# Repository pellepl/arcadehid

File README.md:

arcadehid
=========

STM32 HID device for arcade builds

Compound HID device containing keyboard, mouse, two joysticks and a virtual com port. Plug into a retropie or something and wire cool buttons and joysticks and whatnot.

See /cad - here you'll find a reference design with 26 pins for an STM32F1 128kB flash variant. Any STM32F1 board would do, as long as pin-headers are broken out.

Each pin can be configured with combinations of a keyboard keypress, mouse movement or click, or joystick movement or button press.

Every pin can hold up to eight different combinations. There is also ternary support meaning a pin's config can change depending on if another pin is active or not.

Accelerators for mouse and joystick are supported.

Everything is configured in the command line interface, either via UART pins or via virtual com port.

Different configurations can be saved and loaded, using the internal flash of the STM32F1 (128 kb variant) - no extra storage chip needed.

Depends on pellepl/generic_embedded and pellepl/niffs.

Now also with the Annoyatron support, drive your friends mad...

CLI pin definition examples
===========================
```
// define pin 1 to send keyboard character A
def pin1 = a
// define pin 2 to move mouse up
def pin2 = mouse_y(-1)
// define pin 3 to move mouse right if pin 4 is pressed else left
def pin3 = pin4 ? mouse_x(1) : mouse_x(-1)
// define pin 5 to send keyboard sequence CTRL+ALT+DEL
def pin5 = LEFT_CTRL LEFT_ALT DELETE
```

For certain definitions, numerators are possible. A numerators normally tells how much to move something, e.g. a mouse or joystick. In addition, all numerators can have accelerators, meaning the control will move more and more over time.
A numerator ```<num>``` is defined as  ```(ACC)[(+)|-][1..127]```.

```
// move joystick 10 steps right on x axis
def pin7 = joy1_x(10)
// move joystick accelerating from 1 to 10 steps right on x axis
def pin8 = joy1_x(ACC10)
// and left
def pin8 = joy1_x(ACC-10)
```

Accelerator speed is controlled by cli commands
```
set_mouse_pos_acc
set_mouse_wheel_acc
set_joy_acc
```

Following is a list of all definitions possible.

```
KEYBOARD SYMBOLS:
  A                   B                   C                   D                   
  E                   F                   G                   H                   
  I                   J                   K                   L                   
  M                   N                   O                   P                   
  Q                   R                   S                   T                   
  U                   V                   W                   X                   
  Y                   Z                   1                   2                   
  3                   4                   5                   6                   
  7                   8                   9                   0                   
  ENTER               ESCAPE              BACKSPACE           TAB                 
  SPACE               MINUS               EQUAL               LEFTBRACKET         
  RIGHTBRACKET        BACKSLASH           NONUS_HASH          SEMICOLON           
  QUOTE               GRAVE               COMMA               DOT                 
  SLASH               CAPSLOCK            F1                  F2                  
  F3                  F4                  F5                  F6                  
  F7                  F8                  F9                  F10                 
  F11                 F12                 PRINTSCREEN         SCROLLLOCK          
  PAUSE               INSERT              HOME                PGUP                
  DELETE              END                 PGDOWN              RIGHT               
  LEFT                DOWN                UP                  NUMLOCK             
  KP_SLASH            KP_ASTERISK         KP_MINUS            KP_PLUS             
  KP_ENTER            KP_1                KP_2                KP_3                
  KP_4                KP_5                KP_6                KP_7                
  KP_8                KP_9                KP_0                KP_DOT              
  NONUS_BACKSLASH     APPLICATION         POWER               KP_EQUAL            
  F13                 F14                 F15                 F16                 
  F17                 F18                 F19                 F20                 
  F21                 F22                 F23                 F24                 
  EXECUTE             HELP                MENU                SELECT              
  STOP                AGAIN               UNDO                CUT                 
  COPY                PASTE               FIND                MUTE                
  VOLUME_UP           VOLUME_DOWN         LOCKING_CAPS        LOCKING_NUM         
  LOCKING_SCROLL      KP_COMMA            KP_EQUAL_AS400      INT1                
  INT2                INT3                INT4                INT5                
  INT6                INT7                INT8                INT9                
  LANG1               LANG2               LANG3               LANG4               
  LANG5               LANG6               LANG7               LANG8               
  LANG9               ALT_ERASE           SYSREQ              CANCEL              
  CLEAR               PRIOR               RETURN              SEPARATOR           
  OUT                 OPER                CLEAR_AGAIN         CRSEL               
  EXSEL               SYSTEM_POWER        SYSTEM_SLEEP        SYSTEM_WAKE         
  AUDIO_MUTE          AUDIO_VOL_UP        AUDIO_VOL_DOWN      MEDIA_NEXT_TRACK    
  MEDIA_PREV_TRACK    MEDIA_STOP          MEDIA_PLAY_PAUSE    MEDIA_SELECT        
  MEDIA_EJECT         MAIL                CALCULATOR          MY_COMPUTER         
  WWW_SEARCH          WWW_HOME            WWW_BACK            WWW_FORWARD         
  WWW_STOP            WWW_REFRESH         WWW_FAVORITES       MEDIA_FAST_FORWARD  
  MEDIA_REWIND        LEFT_CTRL           LEFT_SHIFT          LEFT_ALT            
  LEFT_GUI            RIGHT_CTRL          RIGHT_SHIFT         RIGHT_ALT           
  RIGHT_GUI           

MOUSE SYMBOLS:
  MOUSE_X(<num>)      MOUSE_Y(<num>)      MOUSE_BUTTON1       MOUSE_BUTTON2       
  MOUSE_BUTTON3       MOUSE_WHEEL(<num>)  

JOYSTICK SYMBOLS:
  JOY1_X(<num>)       JOY1_Y(<num>)       JOY1_BUTTON1        JOY1_BUTTON2        
  JOY1_BUTTON3        JOY1_BUTTON4        JOY1_BUTTON5        JOY1_BUTTON6        
  JOY1_BUTTON7        JOY1_BUTTON8        JOY1_BUTTON9        JOY1_BUTTON10       
  JOY1_BUTTON11       JOY1_BUTTON12       JOY1_BUTTON13       JOY1_BUTTON14       
  JOY2_X(<num>)       JOY2_Y(<num>)       JOY2_BUTTON1        JOY2_BUTTON2        
  JOY2_BUTTON3        JOY2_BUTTON4        JOY2_BUTTON5        JOY2_BUTTON6        
  JOY2_BUTTON7        JOY2_BUTTON8        JOY2_BUTTON9        JOY2_BUTTON10       
  JOY2_BUTTON11       JOY2_BUTTON12       JOY2_BUTTON13       JOY2_BUTTON14
```

## Building ##

Make sure you clone submodules.

```
human-entity@machine ~$ git clone --recursive https://github.com/pellepl/arcadehid
```

You'll need an arm toolchain, let's say it lies in `/home/human-entity/toolchain/arm-none-eabi-toolchain-gcc-6.3.0`.
Then you simply do this:
```
human-entity@machine ~$ cd arcadehid
human-entity@machine ~/arcadehid$ make clean
human-entity@machine ~/arcadehid$ CROSS_COMPILE=/home/human-entity/toolchain/arm-none-eabi-toolchain-gcc-6.3.0/bin/arm-none-eabi- make all
```

Alternatively. you tinker a bit with the makefile.

This will produce target files in elf, binary, and ihex flavours in the `build` folder. Flash using your favourite dongle and tool. I use OpenOCD, there are some scripts in the repo which might be helpful to others.

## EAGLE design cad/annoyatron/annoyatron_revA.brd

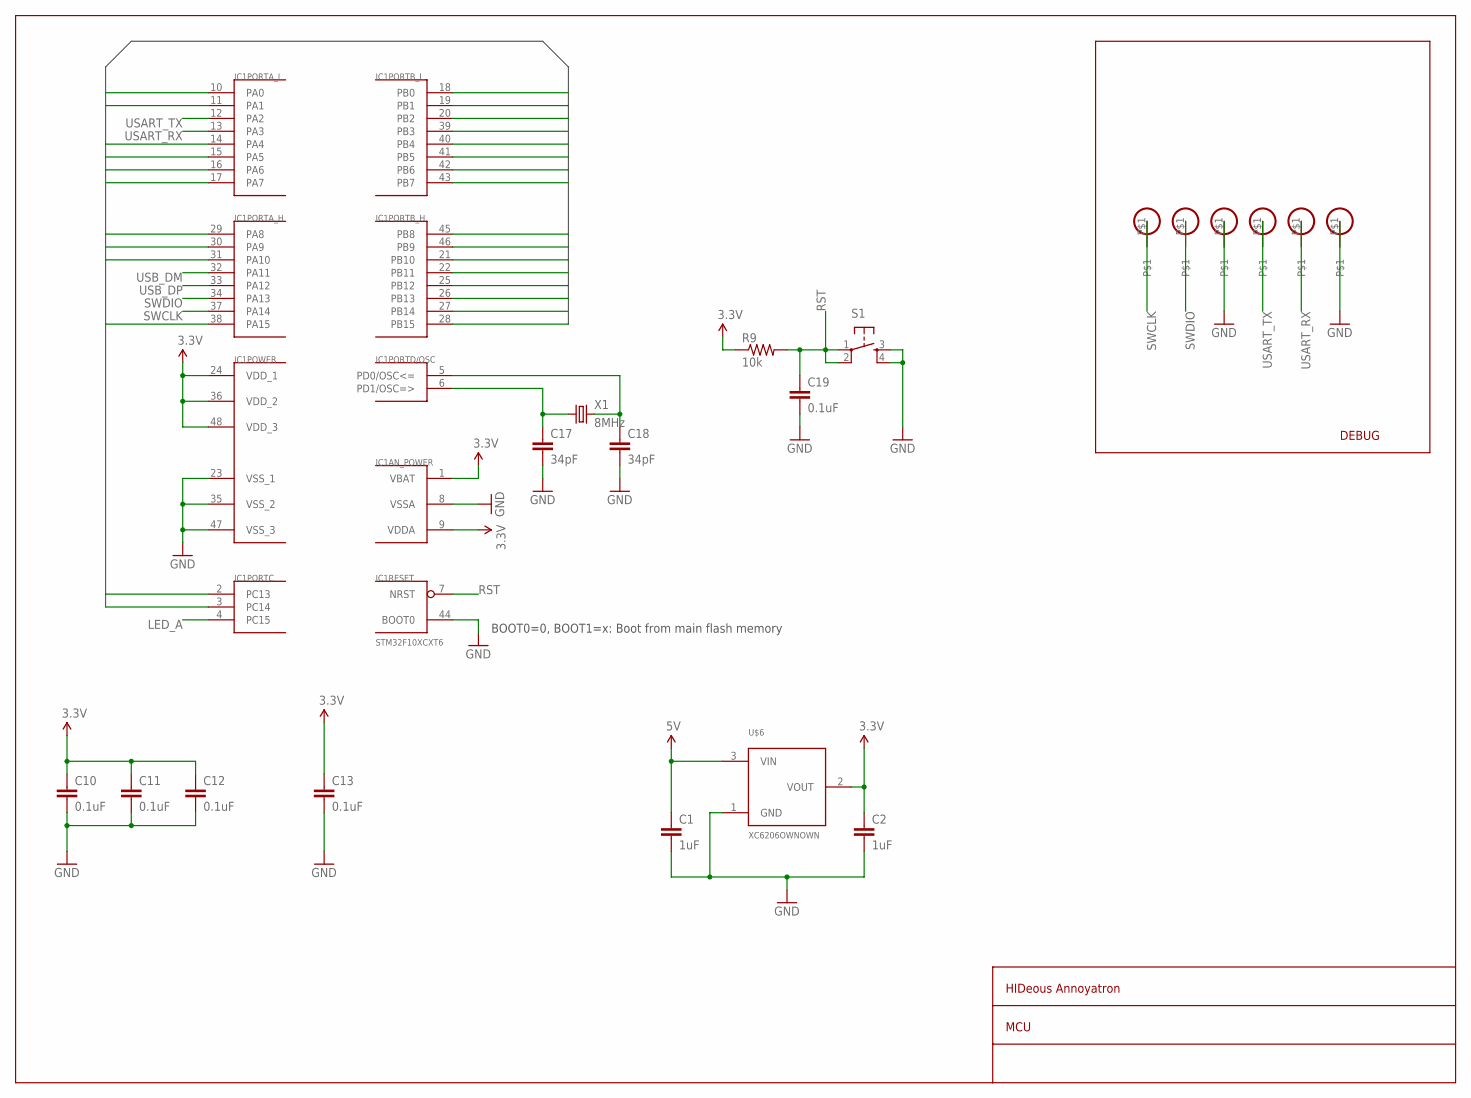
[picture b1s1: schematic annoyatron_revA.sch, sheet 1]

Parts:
C1, C2: 1uF; 0805_GEN
C10, C11, C12, C13, C19: 0.1uF; C0402
C17, C18: 34pF; C0402
IC1: STM32F10XCXT6; TQFP48
R9: 10k; C0402
S1: TAC_SWITCHSMD; TACTILE_SWITCH_SMD
U$2, U$3, U$4, U$5, U$9, U$10: PADOWN; PAD2MM
U$6: XC6206OWNOWN; SOT23
X1: 8MHz; CRYSTAL_SMD_5X3.2_7A

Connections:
3.3V: C2.1, C10.1, C11.1, C12.1, C13.1, IC1.1 (VBAT), IC1.9 (VDDA), IC1.24 (VDD_1), IC1.36 (VDD_2), IC1.48 (VDD_3), R9.1, U$6.2 (VOUT)
5V: C1.1, U$6.3 (VIN); also elsewhere on the board
GND: C1.2, C2.2, C10.2, C11.2, C12.2, C13.2, C17.2, C18.2, C19.2, IC1.8 (VSSA), IC1.23 (VSS_1), IC1.35 (VSS_2), IC1.44 (BOOT0), IC1.47 (VSS_3), S1.3, S1.4, U$4.P$1, U$6.1 (GND), U$10.P$1; also elsewhere on the board
LED_A: IC1.4 (PC15)
OSCI: C18.1, IC1.5 (PD0/OSC<=), X1.P$2 (2)
OSCO: C17.1, IC1.6 (PD1/OSC=>), X1.P$1 (1)
PA0: IC1.10 (PA0)
PA1: IC1.11 (PA1)
PA4: IC1.14 (PA4)
PA5: IC1.15 (PA5)
PA6: IC1.16 (PA6)
PA7: IC1.17 (PA7)
PA8: IC1.29 (PA8); also elsewhere on the board
PA9: IC1.30 (PA9)
PA10: IC1.31 (PA10)
PA15: IC1.38 (PA15)
PB0: IC1.18 (PB0)
PB1: IC1.19 (PB1)
PB2: IC1.20 (PB2)
PB3: IC1.39 (PB3)
PB4: IC1.40 (PB4)
PB5: IC1.41 (PB5)
PB6: IC1.42 (PB6)
PB7: IC1.43 (PB7)
PB8: IC1.45 (PB8)
PB9: IC1.46 (PB9)
PB10: IC1.21 (PB10)
PB11: IC1.22 (PB11)
PB12: IC1.25 (PB12)
PB13: IC1.26 (PB13)
PB14: IC1.27 (PB14)
PB15: IC1.28 (PB15)
PC13: IC1.2 (PC13)
PC14: IC1.3 (PC14)
RST: C19.1, IC1.7 (NRST), R9.2, S1.1, S1.2
SWCLK: IC1.37 (PA14), U$2.P$1
SWDIO: IC1.34 (PA13), U$3.P$1
USART_RX: IC1.13 (PA3), U$9.P$1
USART_TX: IC1.12 (PA2), U$5.P$1
USB_DM: IC1.32 (PA11); also elsewhere on the board
USB_DP: IC1.33 (PA12); also elsewhere on the board

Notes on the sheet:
HIDeous Annoyatron
MCU
DEBUG
BOOT0=0, BOOT1=x: Boot from main flash memory

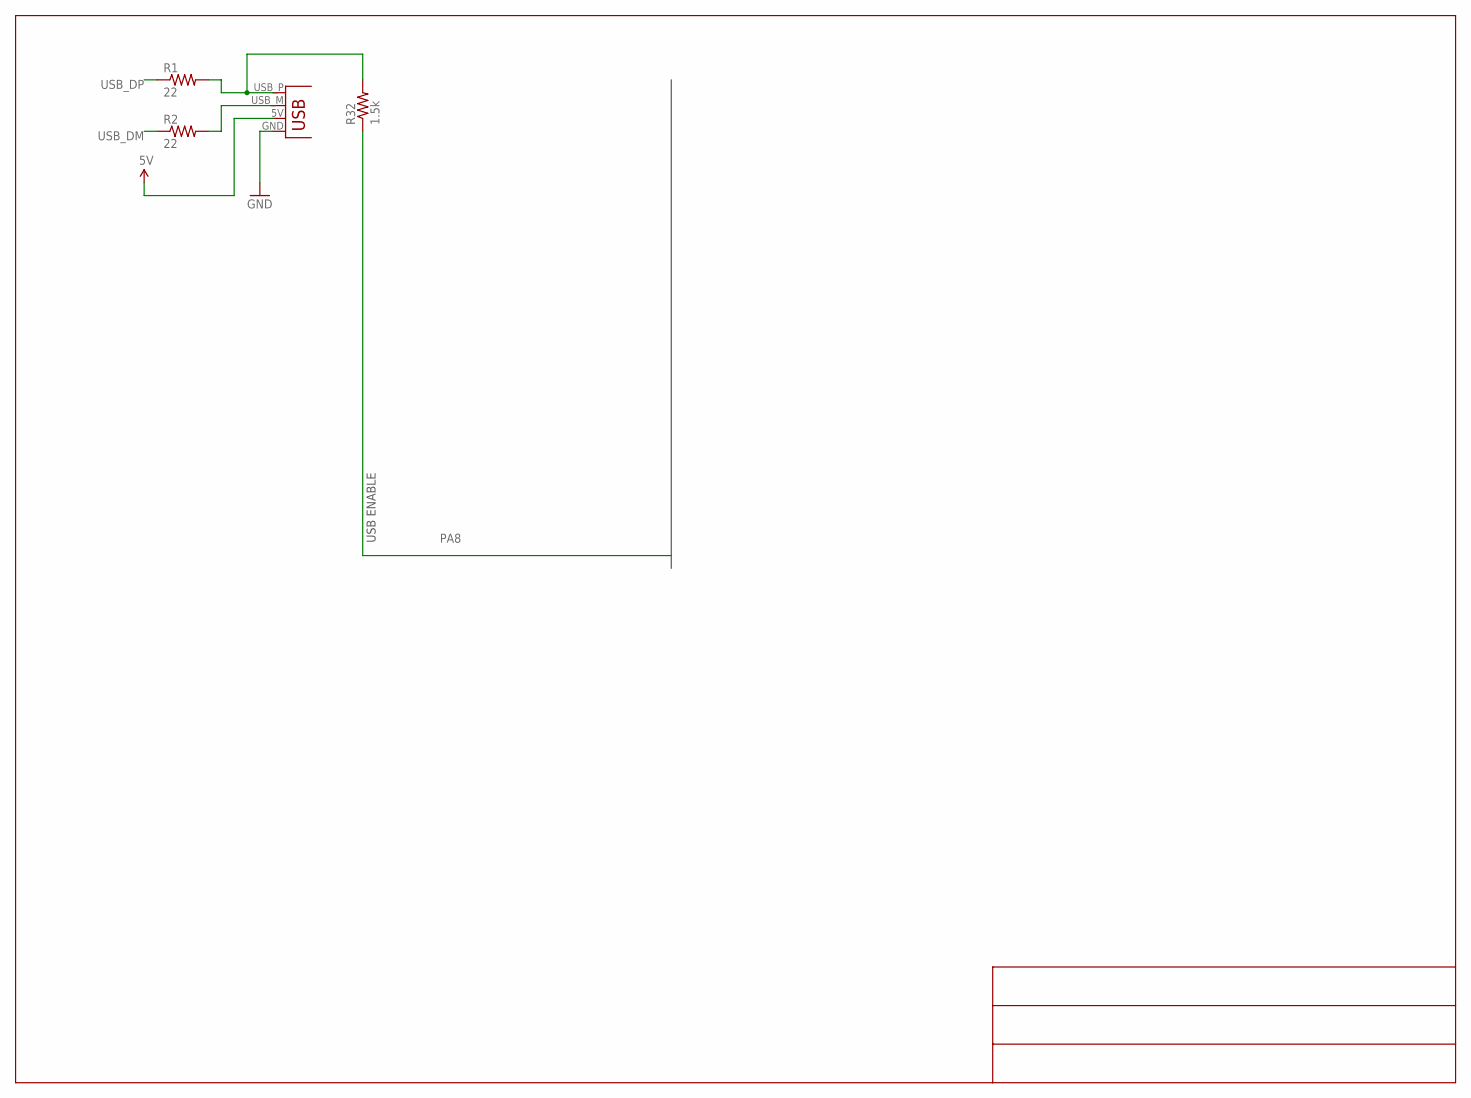
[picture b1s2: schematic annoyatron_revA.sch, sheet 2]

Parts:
JP1: USBPCB; USB-A-PCB
R1, R2: 22; C0402
R32: 1.5k; C0402

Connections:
5V: JP1.5V (VBUS); also elsewhere on the board
GND: JP1.GND; also elsewhere on the board
unnamed: JP1.USB_P (D+), R1.2, R32.2
unnamed: JP1.USB_M (D-), R2.2
PA8: R32.1; also elsewhere on the board
USB_DM: R2.1; also elsewhere on the board
USB_DP: R1.1; also elsewhere on the board

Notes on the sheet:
USB ENABLE

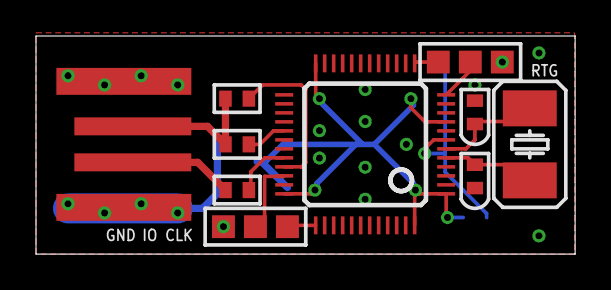
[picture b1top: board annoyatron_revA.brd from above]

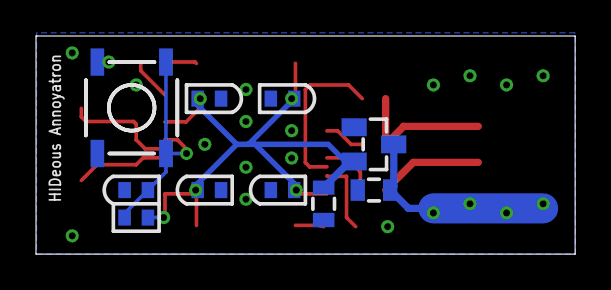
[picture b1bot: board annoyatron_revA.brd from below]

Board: 2 copper layers, 30.0 x 12.1 mm, 24 parts (10 on the bottom side), 15 nets.

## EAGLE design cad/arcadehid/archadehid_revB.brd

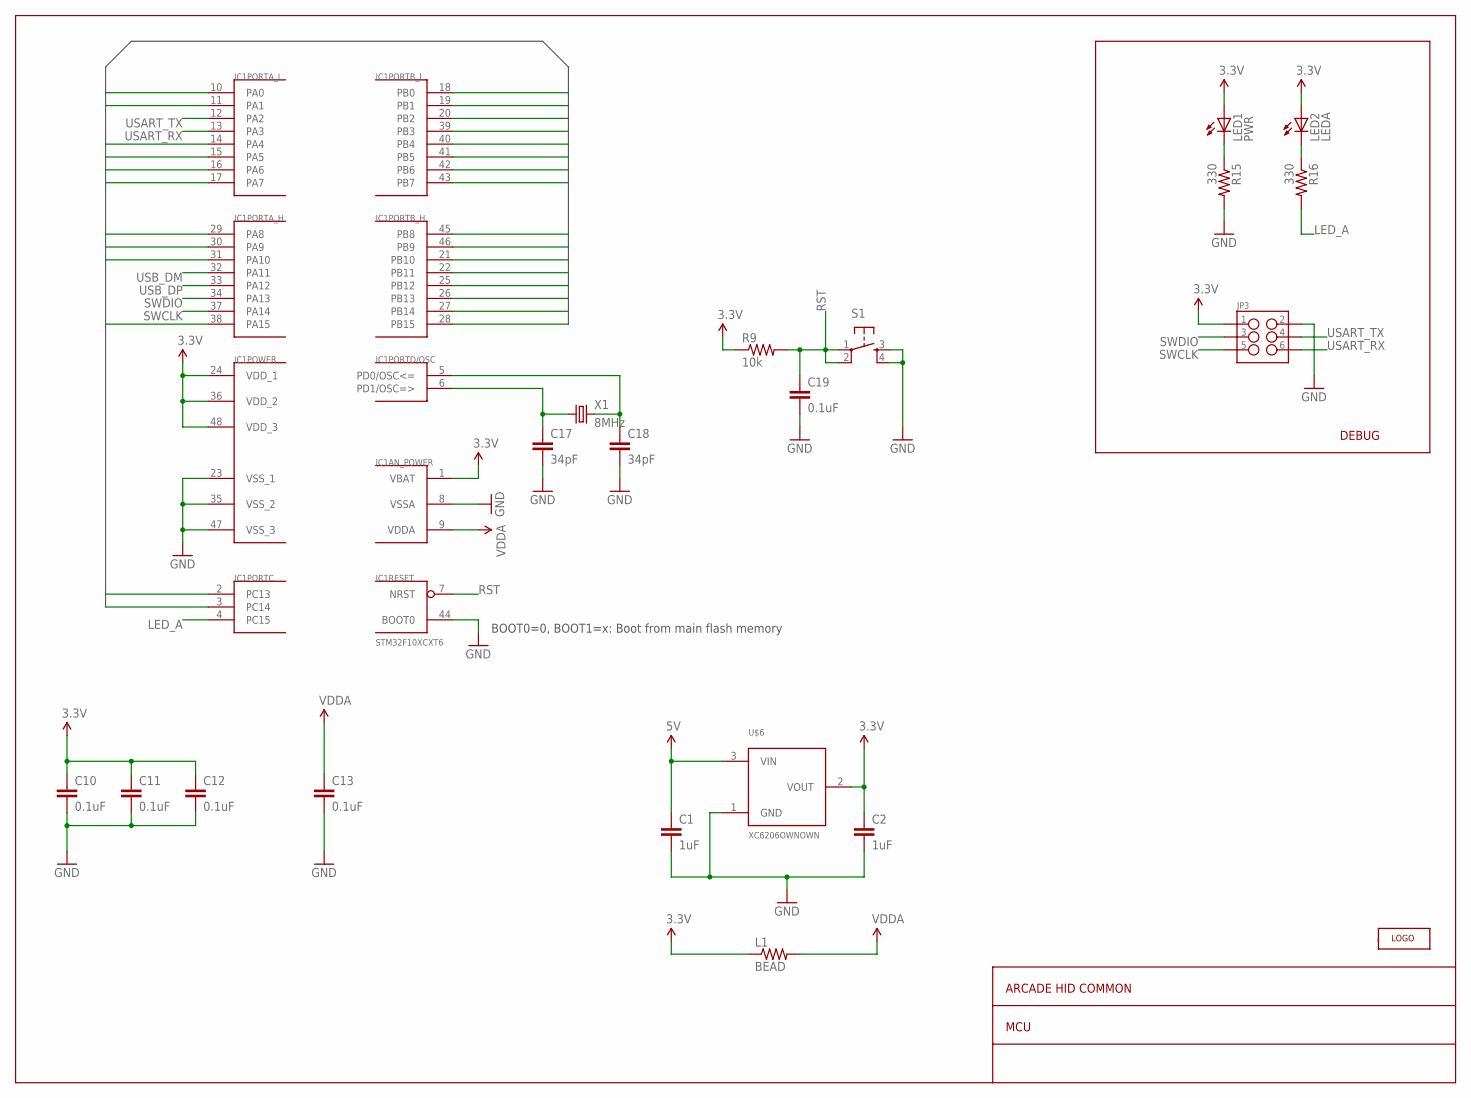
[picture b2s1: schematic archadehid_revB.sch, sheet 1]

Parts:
C1, C2: 1uF; 0805_GEN
C10, C11, C12, C13, C19: 0.1uF; C0402
C17, C18: 34pF; C0402
IC1: STM32F10XCXT6; TQFP48
JP3: M03X2NO_SILK; 2X3-NS
L1: BEAD; 0603_GEN
LED1: PWR; LED-0603
LED2: LEDA; LED-0603
R9: 10k; C0402
R15, R16: 330; C0402
S1: TAC_SWITCHSMD; TACTILE_SWITCH_SMD
U$6: XC6206OWNOWN; SOT23
U$7: LOGOLOGO; LOGO
X1: 8MHz; CRYSTAL_SMD_5X3.2_7A

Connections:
3.3V: C2.1, C10.1, C11.1, C12.1, IC1.1 (VBAT), IC1.24 (VDD_1), IC1.36 (VDD_2), IC1.48 (VDD_3), JP3.1, L1.1, LED1.A, LED2.A, R9.1, U$6.2 (VOUT); also elsewhere on the board
5V: C1.1, U$6.3 (VIN); also elsewhere on the board
GND: C1.2, C2.2, C10.2, C11.2, C12.2, C13.2, C17.2, C18.2, C19.2, IC1.8 (VSSA), IC1.23 (VSS_1), IC1.35 (VSS_2), IC1.44 (BOOT0), IC1.47 (VSS_3), JP3.2, R15.2, S1.3, S1.4, U$6.1 (GND); also elsewhere on the board
LED_A: IC1.4 (PC15), R16.2
unnamed: LED1.C, R15.1
unnamed: LED2.C, R16.1
OSCI: C18.1, IC1.5 (PD0/OSC<=), X1.P$2 (2)
OSCO: C17.1, IC1.6 (PD1/OSC=>), X1.P$1 (1)
PA0: IC1.10 (PA0); also elsewhere on the board
PA1: IC1.11 (PA1); also elsewhere on the board
PA4: IC1.14 (PA4); also elsewhere on the board
PA5: IC1.15 (PA5); also elsewhere on the board
PA6: IC1.16 (PA6); also elsewhere on the board
PA7: IC1.17 (PA7); also elsewhere on the board
PA8: IC1.29 (PA8); also elsewhere on the board
PA9: IC1.30 (PA9); also elsewhere on the board
PA10: IC1.31 (PA10); also elsewhere on the board
PA15: IC1.38 (PA15); also elsewhere on the board
PB0: IC1.18 (PB0); also elsewhere on the board
PB1: IC1.19 (PB1); also elsewhere on the board
PB2: IC1.20 (PB2); also elsewhere on the board
PB3: IC1.39 (PB3); also elsewhere on the board
PB4: IC1.40 (PB4); also elsewhere on the board
PB5: IC1.41 (PB5); also elsewhere on the board
PB6: IC1.42 (PB6); also elsewhere on the board
PB7: IC1.43 (PB7); also elsewhere on the board
PB8: IC1.45 (PB8)
PB9: IC1.46 (PB9); also elsewhere on the board
PB10: IC1.21 (PB10); also elsewhere on the board
PB11: IC1.22 (PB11); also elsewhere on the board
PB12: IC1.25 (PB12); also elsewhere on the board
PB13: IC1.26 (PB13); also elsewhere on the board
PB14: IC1.27 (PB14); also elsewhere on the board
PB15: IC1.28 (PB15); also elsewhere on the board
PC13: IC1.2 (PC13); also elsewhere on the board
PC14: IC1.3 (PC14); also elsewhere on the board
RST: C19.1, IC1.7 (NRST), R9.2, S1.1, S1.2
SWCLK: IC1.37 (PA14), JP3.5
SWDIO: IC1.34 (PA13), JP3.3
USART_RX: IC1.13 (PA3), JP3.6
USART_TX: IC1.12 (PA2), JP3.4
USB_DM: IC1.32 (PA11); also elsewhere on the board
USB_DP: IC1.33 (PA12); also elsewhere on the board
VDDA: C13.1, IC1.9 (VDDA), L1.2

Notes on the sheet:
ARCADE HID COMMON
MCU
DEBUG
BOOT0=0, BOOT1=x: Boot from main flash memory

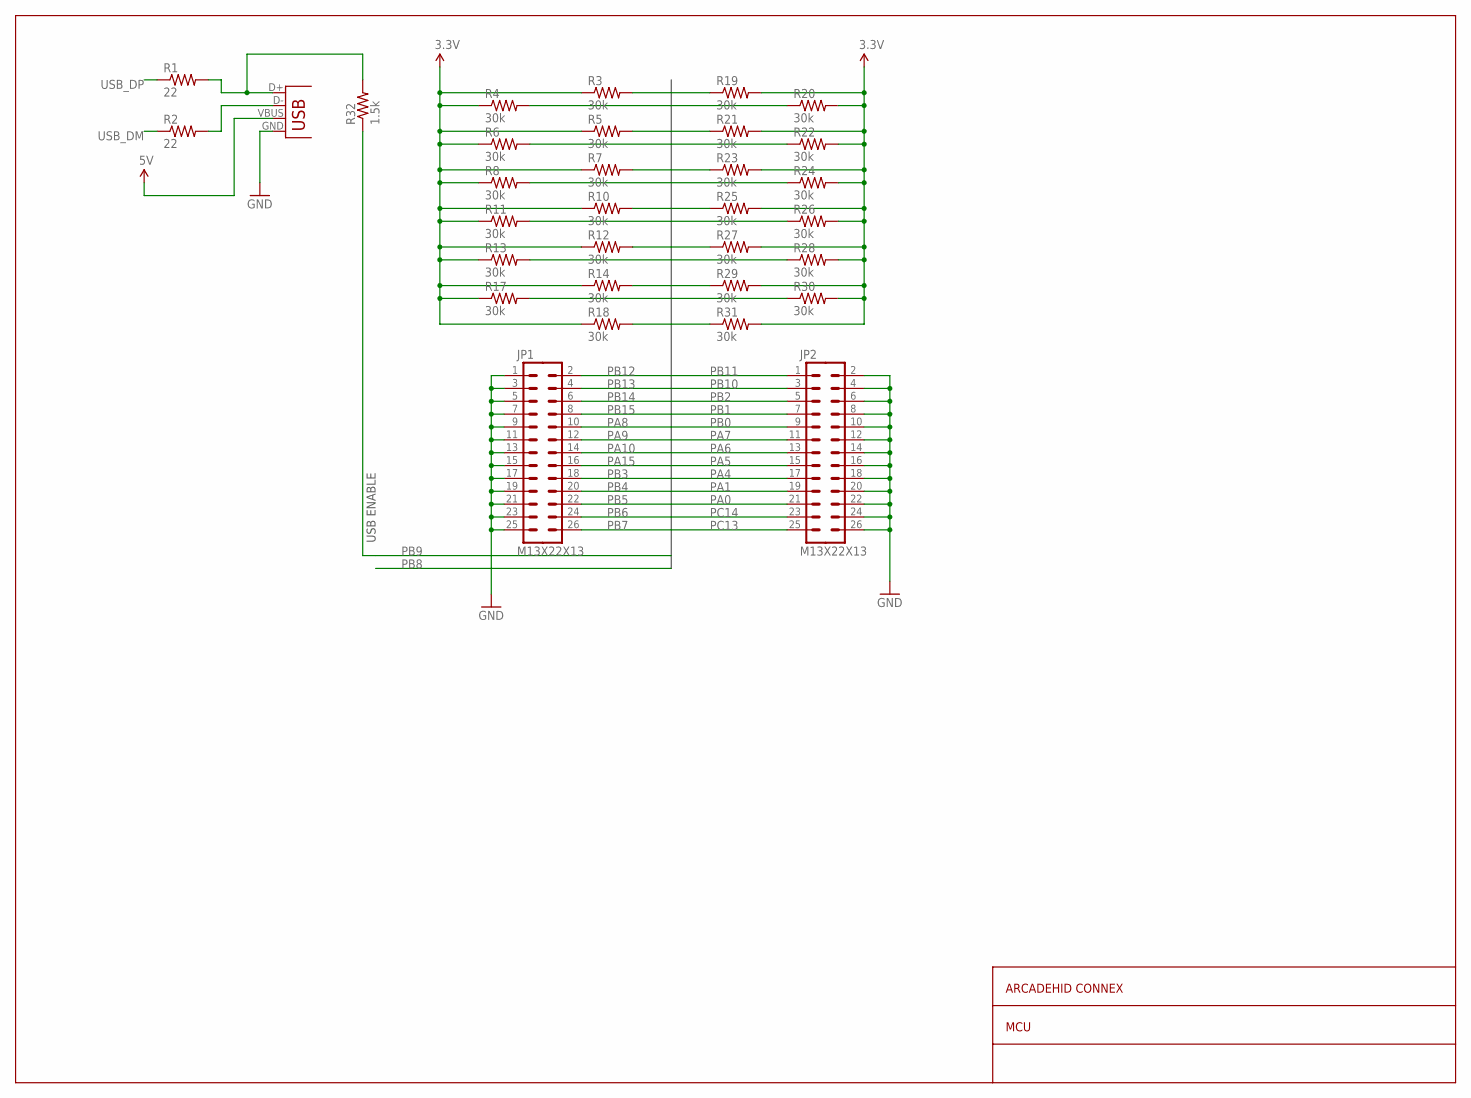
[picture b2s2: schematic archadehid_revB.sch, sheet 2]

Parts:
JP1, JP2: M13X22X13; 2X13
R1, R2: 22; C0402
R3, R4, R5, R6, R7, R8, R10, R11, R12, R13, R14, R17, R18, R19, R20, R21, R22, R23, R24, R25, R26, R27, R28, R29, R30, R31: 30k; C0402
R32: 1.5k; C0402
X3: USB-MINIB

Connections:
3.3V: R3.1, R4.1, R5.1, R6.1, R7.1, R8.1, R10.1, R11.1, R12.1, R13.1, R14.1, R17.1, R18.1, R19.2, R20.2, R21.2, R22.2, R23.2, R24.2, R25.2, R26.2, R27.2, R28.2, R29.2, R30.2, R31.2; also elsewhere on the board
5V: X3.VBUS; also elsewhere on the board
GND: JP1.1, JP1.3, JP1.5, JP1.7, JP1.9, JP1.11, JP1.13, JP1.15, JP1.17, JP1.19, JP1.21, JP1.23, JP1.25, JP2.2, JP2.4, JP2.6, JP2.8, JP2.10, JP2.12, JP2.14, JP2.16, JP2.18, JP2.20, JP2.22, JP2.24, JP2.26, X3.GND; also elsewhere on the board
unnamed: R1.2, R32.2, X3.D+
unnamed: R2.2, X3.D-
PA0: JP2.21, R29.1; also elsewhere on the board
PA1: JP2.19, R28.1; also elsewhere on the board
PA4: JP2.17, R27.1; also elsewhere on the board
PA5: JP2.15, R26.1; also elsewhere on the board
PA6: JP2.13, R25.1; also elsewhere on the board
PA7: JP2.11, R24.1; also elsewhere on the board
PA8: JP1.10, R7.2; also elsewhere on the board
PA9: JP1.12, R8.2; also elsewhere on the board
PA10: JP1.14, R10.2; also elsewhere on the board
PA15: JP1.16, R11.2; also elsewhere on the board
PB0: JP2.9, R23.1; also elsewhere on the board
PB1: JP2.7, R22.1; also elsewhere on the board
PB2: JP2.5, R21.1; also elsewhere on the board
PB3: JP1.18, R12.2; also elsewhere on the board
PB4: JP1.20, R13.2; also elsewhere on the board
PB5: JP1.22, R14.2; also elsewhere on the board
PB6: JP1.24, R17.2; also elsewhere on the board
PB7: JP1.26, R18.2; also elsewhere on the board
PB9: R32.1; also elsewhere on the board
PB10: JP2.3, R20.1; also elsewhere on the board
PB11: JP2.1, R19.1; also elsewhere on the board
PB12: JP1.2, R3.2; also elsewhere on the board
PB13: JP1.4, R4.2; also elsewhere on the board
PB14: JP1.6, R5.2; also elsewhere on the board
PB15: JP1.8, R6.2; also elsewhere on the board
PC13: JP2.25, R31.1; also elsewhere on the board
PC14: JP2.23, R30.1; also elsewhere on the board
USB_DM: R2.1; also elsewhere on the board
USB_DP: R1.1; also elsewhere on the board

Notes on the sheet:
ARCADEHID CONNEX
MCU
USB ENABLE

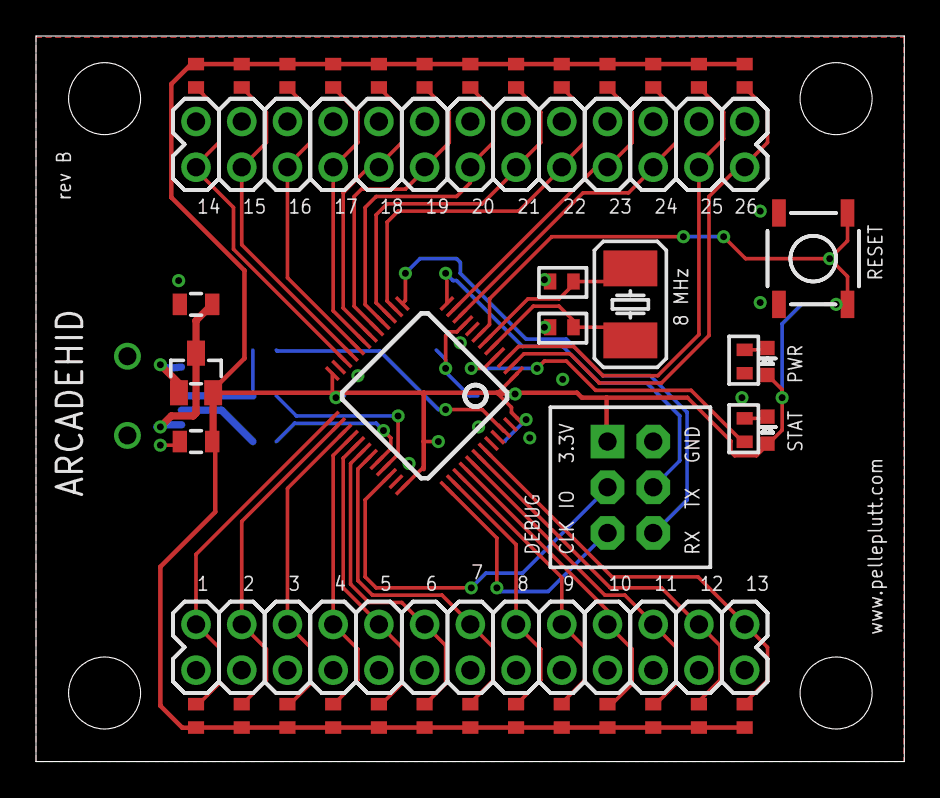
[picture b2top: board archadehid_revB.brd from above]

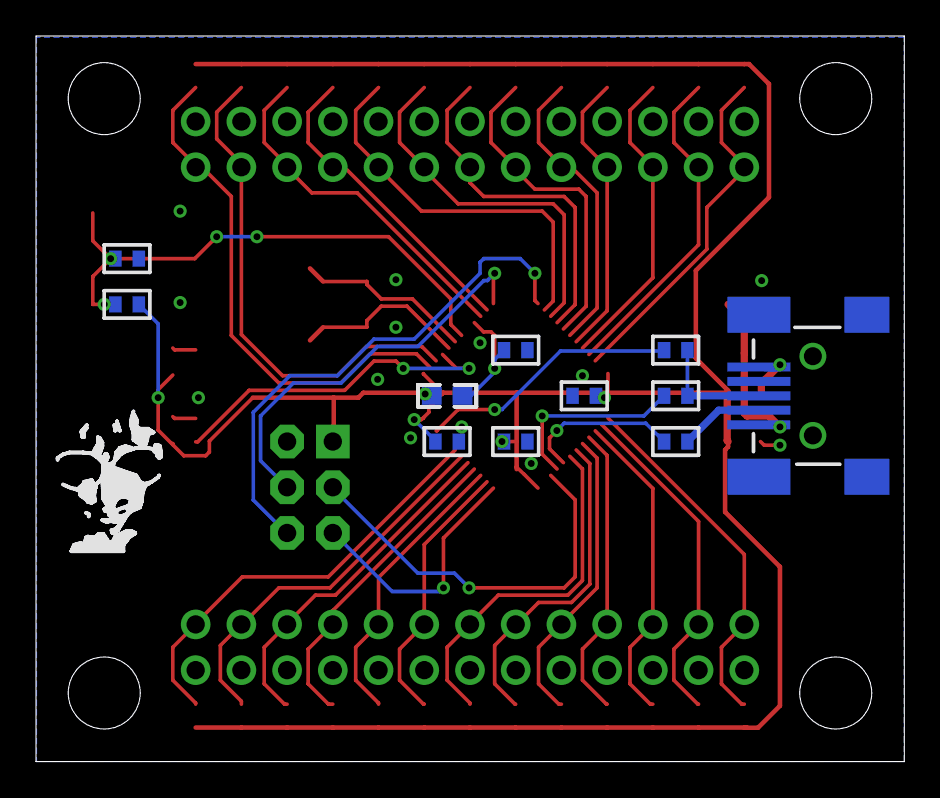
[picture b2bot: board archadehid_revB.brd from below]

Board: 2 copper layers, 48.2 x 40.3 mm, 53 parts (12 on the bottom side), 45 nets.

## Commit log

2014-12-29 inital commit
2014-12-29 cleanup, reset @ assert
2014-12-30 getting ledstate
2015-01-02 added mouse configuration
2015-01-07 cadding, almost there
2015-01-07 minor cleanups
2015-01-08 cad, rev A to factory
2015-01-09 embryo for adding usb vcd, build configurable
2015-01-09 usb cdc acm profile working
2015-01-09 added usb serial as io
2015-01-09 clean away windows lineendings
2015-01-11 fixed up usb PMA buffer sizes
2015-01-11 cli over usb, more app preparing
2015-01-14 added cli test for trying keyboard map
2015-01-20 added parser for keyboard, inital step
2015-01-25 gpio deffing, key handling - still bugs, sticky keys
2015-01-26 key handling, getting there, mouse started
2015-01-26 renamed, cleanup of pintrigging
2015-01-26 fixed gpiotrigging error, trigger on state instead of debouncer
2015-01-27 mouse stuff started
2015-02-01 added board rev A scripts and dbg, fixed accelerator and mouse
2015-02-01 fixed hy board jtag PB3, cleaned upp cli, added help texts
2015-02-02 cleaned away unwanted inclusions
2015-02-02 more debug, configuration
2015-02-02 cad, rev B
2015-02-02 hide debug commands when not @ dbg level
2015-02-03 fixed accelerators
2015-02-04 cadded the annoyatron
2015-02-06 preparing for joystick support
2015-02-06 added double usb joysticks
2015-02-06 added app glue for joystick control
2015-02-06 paving way for joystick app, added parsing
2015-02-07 app joystick skeleton
2015-02-08 joystick almost working, needs resetting also (flank & level)
2015-02-28 file system support, some bug fixing
2015-03-01 boosted wear leveling as long as we have no cache
2015-03-02 default config, redesign of pinhandling started
2015-03-03 well, done it seems
2015-03-03 and some minor joystick updates
2015-03-04 last fixes
2015-03-10 annoyatron support added, bwaahaha
2015-03-13 readme.md update
2015-03-23 more annoy scripts, fixed a cli bug when scripting
2018-04-08 added submodules, massaged it all a bit
2018-04-08 Added elfs, binaries, and hexes for v1.1
    fixes #1

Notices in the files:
parts and their libraries:
SparkFun-Electromechanical: Licensing: CC v3.0 Share-Alike You are welcome to use this library for commercial purposes.
